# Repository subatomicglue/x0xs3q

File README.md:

# x0xs3q

We are creating a standalone [x0xb0x](https://www.ladyada.net/make/x0xb0x/) s3quencer.   **Please contribute!**

The idea is a single circuit board with power, USB, MIDI, track/pattern, and the sequencer section of the original x0xb0x.  Embeddable into many styles of case, but targeting a 303 style case to start.

## Features / Goals
- Control other synths via MIDI out:
  - Starting with the Behringer td-3, or midi enabled TB303
  - Also support other mono synths (SH-101, etc)
- Select button mapping with a switch:
  - x0xb0x: the more intuitive style of interface found on the stock x0xb0x (which promotes intentional composition)
  - 303: the more difficult tb303 / td3 style interface (which promotes "happy accidents")
- Slim 303 case
  - in the style of original Roland TB303
  - so that putting the x0xb0x sequencer in front of a TB303 or TD-3 looks like it belongs as a natural extension

## Concept

## Status

- Vaporware, you're looking at it, yes it's just a README so far... and ideas!
- Looking for contributors!

# copyright

this modification is built on the hard work of [Limor Freid](https://www.adafruit.com/about) & [Adafruit](https://www.adafruit.com/), and the [x0xb0x](https://www.ladyada.net/make/x0xb0x/) community

These files are all released under the [MIT Open Source license](http://en.wikipedia.org/wiki/MIT_License):

```
Copyright (c) Limor Fried & Adafruit industries

Permission is hereby granted, free of charge, to any person obtaining a copy of this software, firmware, layout and associated documentation files (the "Design files"), to deal in the Design files without restriction, including without limitation the rights to use, copy, modify, merge, publish, distribute, sublicense, and/or sell copies of the Design, and to permit persons to whom the Design is furnished to do so, subject to the following conditions: The above copyright notice and this permission notice shall be included in all copies or substantial portions of the Design.

THE DESIGN FILES ARE PROVIDED "AS IS", WITHOUT WARRANTY OF ANY KIND, EXPRESS OR IMPLIED, INCLUDING BUT NOT LIMITED TO THE WARRANTIES OF MERCHANTABILITY, FITNESS FOR A PARTICULAR PURPOSE AND NONINFRINGEMENT. IN NO EVENT SHALL THE AUTHORS OR COPYRIGHT HOLDERS BE LIABLE FOR ANY CLAIM, DAMAGES OR OTHER LIABILITY, WHETHER IN AN ACTION OF CONTRACT, TORT OR OTHERWISE, ARISING FROM, OUT OF OR IN CONNECTION WITH THE SOFTWARE OR THE USE OR OTHER DEALINGS IN THE SOFTWARE.
```

Notably:
```
If you plan to make, sell or manufacture x0xb0xes please contact us - we request that you credit Adafruit Industries on the documentation, supporting pages and circuit boards "Copyright (c) Limor Fried & Adafruit industries". x0xb0x (TM) is a trademarked name of Adafruit Industries. Please contact support@adafruit.com if you wish to seek permission to use the name for your products or projects, otherwise you cannot call your product "x0xb0x".
```

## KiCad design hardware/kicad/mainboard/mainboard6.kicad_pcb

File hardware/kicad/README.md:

# what's this

ladyada's original [x0xb0x](https://www.ladyada.net/make/x0xb0x/) mainboard and ioboard files were created with a version of EAGLE older than ver6.

EAGLE is now owned by autodesk, and is only available with FUSION 360 which costs money...

Let's use the excellent free/opensource KiCAD tool instead!

How we converted to KiCAD:
 - we loaded the original LadyAda mainboard and ioboard files into EAGLE 6 freeware, and saved.
 - we then imported the EAGLE6 files into KiCAD 5.1.2

enjoy

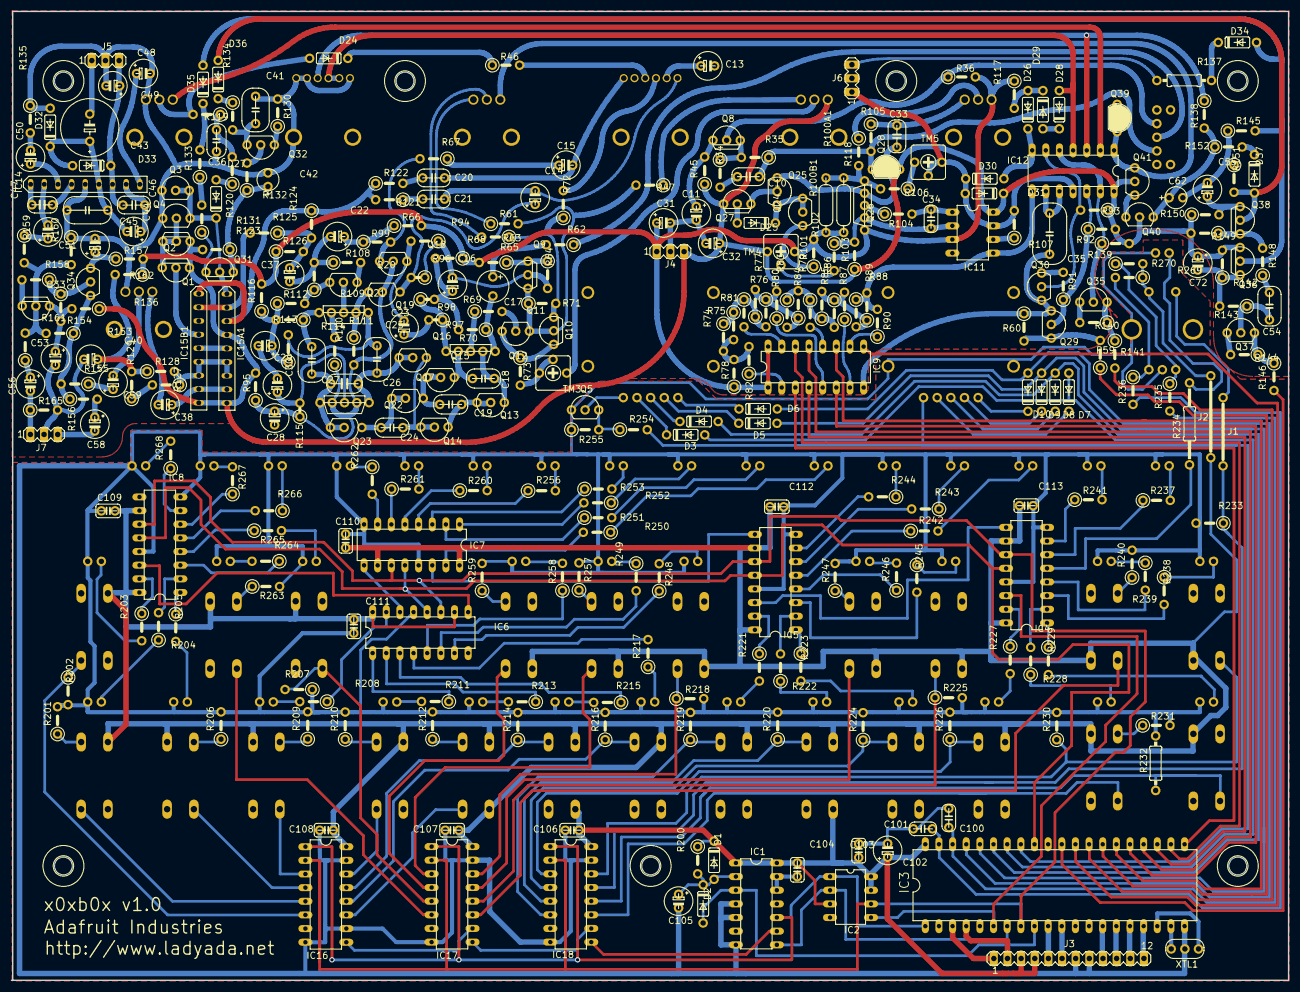
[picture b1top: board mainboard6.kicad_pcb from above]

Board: 16 copper layers, 237.5 x 180.3 mm, 417 parts (0 on the bottom side), 324 nets.

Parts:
C10, C20, C21, C33, C46: .01; C050-024X044
C11, C13, C14, C15, C22, C23, C29, C38, C56, C58, C59, C105: 1/50; E5-6
C16, C30, C31, C32, C37, C40, C50, C52, C72: 10/16; E5-6
C17: 1/50; E3,5-8
C18: .018; C050-025X075
C19, C24, C36: .033; C050-025X075
C25, C27, C41: .1; C050-030X075
C26: .033; C075-032X103
C28, C44, C53, C55: 47/16; E5-6
C34, C100, C101: .001; C050-035X075
C35: .22; C050-045X075
C42, C62: 1/35; E2,5-7
C43: 1000/6.3; E5-5
C45: .068; C050-050X075
C47: .0068; C050-075X075
C48, C49: 100/6.3; E5-6
C51: 2.2/50; E5-6
C54: .047; C050-055X075
C102: 100/10; E5-6
C103, C104, C106, C107, C108, C109, C110, C111, C112, C113: .1; C050H075X075
D1, D2, D3, D4, D5, D6, D7, D8, D9, D10, D24, D25, D26, D27, D28, D29, D30, D31, D32, D33, D34, D35, D36, D37: 1N4148; DO35-10
IC1: 74126N; DIL14
IC2: AT25P; DIL08
IC3: MEGA162P; DIL40
IC4, IC5, IC6, IC7, IC8: 74595N; DIL16
IC9: 4174P; DIL16
IC11: AN6562N; DIL08
IC12: 4066N; DIL14
IC14: LA44140; SIP9
IC15A1: BA662; SIP9
IC15B1: BA6110; SIP9
IC16, IC17, IC18: 74165N; DIL16
J1: J12MM; 12
J2: J15MM; 15
J3: MA12-1
J4, J5, J6, J7: MA03-1
LED1, LED2, LED3, LED4, LED5, LED6, LED7, LED8, LED9, LED10, LED11, LED12, LED13, LED14, LED15, LED16, LED17, LED18, LED19, LED20, LED21, LED22, LED23, LED24, LED25, LED26, LED27, LED28, LED29, LED30, LED31, LED32, LED33, LED34, LED35, LED36, LED37, LED38, LED39, LED40: LED5MM
Q1, Q2, Q8, Q9, Q10, Q27, Q31, Q33, Q36, Q38: 2SA733P; TO92
Q3, Q4, Q5, Q11, Q13, Q14, Q15, Q16, Q18, Q20, Q24, Q25, Q29, Q30, Q32, Q34, Q35, Q37, Q40, Q41: 2SC536F
Q12, Q21, Q26: 2SC1583; SSIP5
Q17, Q23: 2SC536F; 2SC536_UNEVEN
Q19: 2SC536FUNEVEN; 2SC536_UNEVEN
Q22: 2SC2291; SSIP5
Q28, Q39: 2SK30
R34, R36, R47, R61, R64, R65, R94, R101, R105, R109, R112, R116, R142, R143, R144, R145, R148, R149, R201, R202, R203, R204, R205, R206, R207, R208, R209, R210, R211, R212, R213, R214, R215, R216, R217, R218, R219, R220, R221, R222, R223, R224, R225, R226, R227, R228, R229, R230, R231, R233, R237, R238, R239, R240, R241, R242, R243, R244, R245, R246, R247, R248, R249, R250, R251, R252, R253, R254, R255, R256, R257, R258, R259, R260, R261, R262, R263, R264, R265, R266, R267, R268, R269, R270: 10K; 0207_5V
R35, R59, R66, R72, R73, R92, R93, R99, R102, R113, R114, R118, R122, R139, R140, R141, R154, R156, R165: 100K; 0207_5V
R45, R60, R110, R111, R117, R129, R134, R146, R151: 22K; 0207_5V
R46, R119, R127, R155: 47K; 0207_5V
R62, R63, R121, R128, R131: 220K; 0207_5V
R67, R68, R69, R70, R71, R104, R107, R108, R124, R125, R126, R133, R162: 2.2K; 0207_5V
R74, R75, R76, R77, R78, R79, R80, R81, R82, R83, R84, R85, R86, R87, R88, R89: 200K; 0207_5V
R90: 200k; 0207_5V
R91, R200: 1M; 0207_5V
R95, R130, R132, R136, R152: 100; 0207_5V
R96, R97, R115: 10K; 0207_2V
R98: 2.2K; 0207_2V
R100A1, R100B1: THERMISTOR-7,5; R-7,5
R103, R235, R236: 220k; 0207_5V
R106: 27K; 0207_5V
R120: 22k; 0207_5V
R123: 1.5M; 0207_5V
R135: 4.7k; 0207_5V
R137: 1K; 0207_10
R138: 68K; 0207_5V
R150: 22; 0207_5V
R153: 100k; 0207_5V
R157, R158, R160: 10k; 0207_5V
R159: 33K; 0207_5V
R161: 1K; 0207_5V
R232: 10K; 0207_10
R234: 10K; 0207_15
S1: SWITCH_GND; NKKTOGGLE
S2: PEC11-S
S3, S4: GH3074
S5, S6, S7, S8, S9, S10, S11, S12, S13, S14, S15, S16, S17, S18, S19, S20, S21, S22, S23, S24, S25, S26, S27: 40-XX; B3F-40XX
TM3: 500K(B); 306
TM4: 50K(B); 306
TM5: 5K(B); 306
U$2, U$23, U$24, U$25, U$27, U$28, U$29: 1,3
VR2, VR7: 50K(B); EVU
VR3, VR5, VR8: 50K(A); EVU
VR4: 50K(B); ALPHADUAL
VR6: 1M(A); ALPHADUAL
XTL1: 2SC2021R; 2SC2021

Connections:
+5.333V: C31.+, IC9.1, IC9.16, IC11.3, J4.1, Q26.1, R36.2, R65.2, R66.2, R68.1, R78.1, R100A1.2, R100B1.1, R101.2, R116.2, R117.1, R126.1, R157.2, R162.1, TM4.3, VR2.3
+5V: C102.+, C103.1, C104.2, C106.2, C107.2, C108.2, C109.2, C110.2, C111.2, C112.2, C113.2, D1.C, IC1.1, IC1.14, IC2.3, IC2.7, IC2.8, IC3.40, IC4.10, IC4.16, IC5.10, IC5.16, IC6.10, IC6.16, IC7.10, IC7.16, IC8.10, IC8.16, IC16.16, IC17.16, IC18.16, J2.2, J3.3, J3.4, R200.1, S5.2, S6.3, S7.1, S8.1, S9.1, S10.1, S11.1, S12.4, S13.4, S14.2, S15.4, S16.4, S17.2, S18.2, S19.1, S19.2, S20.2, S21.2, S22.1, S22.2, S23.1, S23.2, S24.2, S25.4, S26.4, S27.2
+6V: C46.1, C49.+, D33.C, IC14.7, J5.3
+12V: C32.+, C72.+, D31.C, IC11.8, IC12.14, IC15A1.4, IC15A1.9, IC15B1.9, J4.3, Q1.3, Q2.3, Q27.3, Q28.1, Q36.3, Q40.2, Q41.2, R45.1, R92.2, R93.1, R95.2, R103.1, R123.2, R136.1, R139.2, R142.2, R149.2, R150.1, TM4.1, VR3.3
/ACCENT: IC3.28, R141.2
/DINSYNC1: IC3.17, J3.12
/DINSYNC2: IC3.16, J3.11
/DINSYNC3: IC3.15, J3.10
/DINSYNC4: IC3.14, J3.9
/GATE: IC3.30, R146.2
/LED_LATCH: IC3.32, IC4.12, IC5.12, IC6.12, IC7.12, IC8.12
/MIDI_IN: IC3.10, J3.5
/MIDI_OUT: IC3.11, J3.6
/NOTE0: IC3.21, IC9.3
/NOTE1: IC3.22, IC9.14
/NOTE2: IC3.23, IC9.4
/NOTE3: IC3.24, IC9.13
/NOTE4: IC3.25, IC9.6
/NOTE5: IC3.26, IC9.11
/NOTE_LATCH: IC3.29, IC9.9
/ROTARY1: D3.A, D7.A, IC3.34
/ROTARY2: D4.A, D8.A, IC3.35
/ROTARY4: D5.A, D9.A, IC3.36
/ROTARY8: D6.A, D10.A, IC3.37
/ROTARYCOM3: IC3.33, R254.2, S3.C
/SLIDE: IC3.27, R59.1
/SPI_CLK: IC2.6, IC3.8, IC4.11, IC5.11, IC6.11, IC7.11, IC8.11, IC16.2, IC17.2, IC18.2
/SPI_IN: IC2.5, IC3.6, IC4.14
/SPI_OUT: IC1.8, IC2.2, IC3.7
/SWITCH_LATCH: IC1.10, IC2.1, IC3.1, IC16.1, IC17.1, IC18.1
/TEMPO_SW: IC18.13, J1.2, R233.1
/TEMPO_SW_A: C100.2, IC3.38, R235.2
/TEMPO_SW_B: C101.2, IC3.39, R236.2
/USBRX: IC3.3, J3.1
/USB_TX: IC3.4, J3.2
GND: C11.-, C13.-, C16.-, C22.-, C28.-, C29.-, C30.-, C31.-, C32.-, C33.2, C35.2, C36.2, C37.-, C40.-, C41.2, C42.-, C45.2, C48.-, C49.-, C52.-, C53.-, C55.-, C62.-, C100.1, C101.1, C102.-, C103.2, C104.1, C105.-, C106.1, C107.1, C108.1, C109.1, C110.1, C111.1, C112.1, C113.1, D26.C, D30.A, D32.A, IC1.4, IC1.5, IC1.7, IC1.12, IC1.13, IC2.4, IC3.20, IC4.8, IC4.13, IC5.8, IC5.13, IC6.8, IC6.13, IC7.8, IC7.13, IC8.8, IC8.13, IC9.8, IC11.4, IC12.7, IC14.5, IC15A1.5, IC15B1.3, IC15B1.5, IC16.8, IC16.10, IC16.15, IC17.8, IC17.15, IC18.8, IC18.15, J3.7, J3.8, J4.2, J5.2, J6.2, J7.2, LED1.K, LED2.K, LED3.K, LED4.K, LED5.K, LED6.K, LED7.K, LED8.K, LED9.K, LED10.K, LED11.K, LED12.K, LED13.K, LED14.K, LED15.K, LED16.K, LED17.K, LED18.K, LED19.K, LED20.K, LED21.K, LED22.K, LED23.K, LED24.K, LED25.K, LED26.K, LED27.K, LED28.K, LED29.K, LED30.K, LED31.K, LED32.K, LED33.K, LED34.K, LED35.K, LED36.K, LED37.K, LED38.K, LED39.K, LED40.K, Q3.3, Q4.3, Q5.3, Q9.2, Q29.3, Q30.3, Q35.3, Q37.3, Q39.2, Q39.3, R60.1, R64.2, R94.1, R96.1, R105.1, R108.1, R109.2, R130.2, R135.1, R140.2, R144.2, R145.1, R151.1, R160.1, R165.2, R201.2, R202.2, R206.2, R207.1, R209.2, R210.2, R212.2, R214.2, R216.2, R218.2, R219.2, R220.2, R224.2, R225.2, R226.2, R230.2, R231.2, R232.2, R233.2, R240.2, R247.2, R255.1, R257.2, R259.2, R263.2, S1.M1, S1.M2, S1.M3, S1.M4, S2.C, S2.P$1, S2.P$2, S3.MT1, S3.MT2, S3.MT3, S3.MT4, S4.MT1, S4.MT2, S4.MT3, S4.MT4, VR2.1, VR2.M1, VR2.M2, VR3.M1, VR3.M2, VR4.1A, VR4.M1, VR4.M2, VR5.M1, VR5.M2, VR6.1A, VR6.2A, VR6.3A, VR6.M1, VR6.M2, VR7.1, VR7.M1, VR7.M2, VR8.1, VR8.M1, VR8.M2, XTL1.2
unnamed: C10.1, Q28.3, R35.1, R105.2, S1.1
unnamed: C10.2, R34.2
unnamed: C11.+, Q8.3, R45.2
unnamed: C13.+, VR4.3B
unnamed: C14.+, Q19.3, R96.2
unnamed: C14.-, C21.2, VR4.3A
unnamed: C15.+, R67.1
unnamed: C15.-, C20.2, VR4.2A
unnamed: C16.+, R68.2, R70.2, R98.2
unnamed: C17.+, R62.2
unnamed: C17.-, Q12.1, R70.1
unnamed: C18.1, Q12.4, Q15.3
unnamed: C18.2, Q12.2, Q13.3
unnamed: C19.1, Q13.1, Q13.2, Q14.3
unnamed: C19.2, Q15.1, Q15.2, Q17.3
unnamed: C20.1, R122.2
unnamed: C21.1, R121.1
unnamed: C22.+, R66.1, R99.1
unnamed: C23.+, R97.2
unnamed: C23.-, R94.2
unnamed: C24.1, Q14.1, Q14.2, Q16.3
unnamed: C24.2, Q17.1, Q17.2, Q23.3
unnamed: C25.1, C26.1, Q16.1, Q16.2, Q22.1
unnamed: C25.2, Q21.1, R114.2
unnamed: C26.2, C27.1, Q22.5, Q23.1, Q23.2
unnamed: C27.2, Q21.5, R113.1
unnamed: C28.+, Q18.2, Q19.2, Q22.2, Q22.4, R95.1, R110.2, R111.1, R115.1
unnamed: C29.+, R112.1, R113.2, R114.1, R116.1
unnamed: C30.+, Q22.3, R115.2
unnamed: C33.1, Q25.3, Q26.4, Q28.2
unnamed: C34.1, IC11.1, R104.2
unnamed: C34.2, IC11.2, Q26.2, R102.1, R103.2
unnamed: C35.1, IC12.9, IC12.10
unnamed: C36.1, R119.1, R120.2
unnamed: C37.+, R124.2, R125.1, R126.2
unnamed: C38.+, IC15A1.8, IC15B1.8
unnamed: C38.-, VR8.3
unnamed: C40.+, R128.1, R162.2
unnamed: C41.1, Q32.1, R134.2
unnamed: C42.+, Q31.1, R123.1, R132.1
unnamed: C43.+, C44.-, C45.1, D32.C, D33.A, IC14.6
unnamed: C43.-, J5.1
unnamed: C44.+, C46.2, IC14.8
unnamed: C47.1, IC14.4
unnamed: C47.2, IC14.1
unnamed: C48.+, IC14.9
unnamed: C50.+, IC14.3
unnamed: C50.-, R135.2
unnamed: C51.+, R159.1
unnamed: C51.-, IC14.2
unnamed: C52.+, Q34.1, R157.1
unnamed: C53.+, Q33.3, R136.2, R154.2
unnamed: C54.1, R148.1
unnamed: C54.2, Q37.2, R143.1
unnamed: C55.+, Q38.3, R150.2
unnamed: C56.+, R161.1
unnamed: C58.+, R156.2
unnamed: C58.-, J7.3
unnamed: C59.+, R155.1
unnamed: C59.-, VR8.2
unnamed: C62.+, Q40.1, R138.2, R152.1
unnamed: C105.+, D1.A, D2.C, IC1.2, R200.2
unnamed: D2.A, IC1.3, IC3.9
unnamed: D3.C, S4.P$1
unnamed: D4.C, S4.P$2
unnamed: D5.C, S4.P$4
unnamed: D6.C, S4.P$8
unnamed: D7.C, S3.P$1
unnamed: D8.C, S3.P$2
unnamed: D9.C, S3.P$4
unnamed: D10.C, S3.P$8
unnamed: D24.A, R119.2, VR7.2
unnamed: D24.C, R46.1
unnamed: D25.A, Q27.2
unnamed: D25.C, Q24.1, Q24.2, Q25.1
unnamed: D26.A, D29.C, R117.2
unnamed: D27.A, R120.1
unnamed: D27.C, IC15A1.1, Q3.1, Q3.2, Q4.1, Q31.2
unnamed: D28.A, IC12.4, VR6.2B, VR6.3B
unnamed: D28.C, D29.A
unnamed: D30.C, D31.A, IC11.7, IC12.11, J6.1, R107.2, TM5.2, TM5.3
unnamed: D34.A, D35.A, Q36.2, R145.2
unnamed: D34.C, R137.1
unnamed: D35.C, R133.2
unnamed: D36.A, D37.A, Q38.2, R151.2
unnamed: D36.C, R134.1
unnamed: D37.C, R152.2
unnamed: IC1.9, IC18.9
unnamed: IC3.18, XTL1.3
unnamed: IC3.19, XTL1.1
unnamed: IC4.1, R229.1
unnamed: IC4.2, R228.2
unnamed: IC4.3, R238.2
unnamed: IC4.4, R239.2
unnamed: IC4.5, R234.1
unnamed: IC4.6, R237.1
unnamed: IC4.7, R241.1
unnamed: IC4.9, IC5.14
unnamed: IC4.15, R227.1
unnamed: IC5.1, R223.1
unnamed: IC5.2, R222.2
unnamed: IC5.3, R245.2
unnamed: IC5.4, R246.1
unnamed: IC5.5, R242.1
unnamed: IC5.6, R243.2
unnamed: IC5.7, R244.2
unnamed: IC5.9, IC7.14
unnamed: IC5.15, R221.1
unnamed: IC6.1, R211.1
unnamed: IC6.2, R213.1
unnamed: IC6.3, R215.1
unnamed: IC6.4, R217.2
unnamed: IC6.5, R258.1
unnamed: IC6.6, R249.2
unnamed: IC6.7, R248.1
unnamed: IC6.9, IC8.14
unnamed: IC6.14, IC7.9
unnamed: IC6.15, R208.1
unnamed: IC7.1, R252.2
unnamed: IC7.2, R251.1
unnamed: IC7.3, R253.1
unnamed: IC7.4, R256.1
unnamed: IC7.5, R260.1
unnamed: IC7.6, R261.1
unnamed: IC7.7, R262.2
unnamed: IC7.15, R250.2
unnamed: IC8.1, R205.1
unnamed: IC8.2, R204.2
unnamed: IC8.3, R264.1
unnamed: IC8.4, R265.1
unnamed: IC8.5, R266.2
unnamed: IC8.6, R267.1
unnamed: IC8.7, R268.1
unnamed: IC8.15, R203.1
unnamed: IC9.2, R82.1
unnamed: IC9.5, R80.1
unnamed: IC9.7, R87.1
unnamed: IC9.10, R90.1
unnamed: IC9.12, R79.2
unnamed: IC9.15, R81.2
unnamed: IC11.5, IC12.8, R88.1, R89.2, R90.2
unnamed: IC11.6, R107.1
unnamed: IC12.1, Q39.1, Q41.3, VR5.3
unnamed: IC12.2, VR7.3
unnamed: IC12.3, R138.1, VR6.1B
unnamed: IC12.6, Q30.2, R93.2
unnamed: IC12.12, Q29.2, R91.1, R92.1
unnamed: IC12.5, IC12.13, Q35.2, R139.1
unnamed: IC15A1.2, IC15B1.2, R125.2
unnamed: IC15A1.3, IC15B1.1, R121.2, R122.1, R124.1
unnamed: IC15A1.6, IC15A1.7, IC15B1.6, IC15B1.7, R127.1, R128.2
unnamed: IC15B1.4, Q1.2
unnamed: IC16.3, S25.1
unnamed: IC16.4, S26.1
unnamed: IC16.5, S27.3
unnamed: IC16.6, R202.1, S14.3
unnamed: IC16.9, IC17.10
unnamed: IC16.11, S23.3
unnamed: IC16.12, R216.1, S21.4
unnamed: IC16.13, R214.1, S22.4
unnamed: IC16.14, S24.3
unnamed: IC17.3, S10.3
unnamed: IC17.4, S11.3
unnamed: IC17.5, R207.2, S12.1
unnamed: IC17.6, S13.1
unnamed: IC17.9, IC18.10
unnamed: IC17.11, S6.1
unnamed: IC17.12, R225.1, S7.3
unnamed: IC17.13, S8.3
unnamed: IC17.14, R218.1, S9.3
unnamed: IC18.3, R226.1, S17.4
unnamed: IC18.4, R224.1, S18.4
unnamed: IC18.5, R220.1, S19.4
unnamed: IC18.6, R219.1, S20.4
unnamed: IC18.11, S16.1
unnamed: IC18.12, R232.1, S15.1
unnamed: IC18.14, R230.1, S5.4
unnamed: J1.1, S2.SW1
unnamed: J2.1, R269.1, R270.2, S2.SW2
unnamed: J6.3, R137.2
unnamed: J7.1, R165.1
unnamed: LED1.A, R234.2
unnamed: LED2.A, R237.2
unnamed: LED3.A, R241.2
unnamed: LED4.A, R242.2
unnamed: LED5.A, R243.1
unnamed: LED6.A, R244.1
unnamed: LED7.A, R250.1
unnamed: LED8.A, R251.2
unnamed: LED9.A, R252.1
unnamed: LED10.A, R253.2
unnamed: LED11.A, R256.2
unnamed: LED12.A, R260.2
unnamed: LED13.A, R261.2
unnamed: LED14.A, R262.1
unnamed: LED15.A, R266.1
unnamed: LED16.A, R267.2
unnamed: LED17.A, R268.2
unnamed: LED18.A, R238.1
unnamed: LED19.A, R239.1
unnamed: LED20.A, R245.1
unnamed: LED21.A, R246.2
unnamed: LED22.A, R248.2
unnamed: LED23.A, R249.1
unnamed: LED24.A, R258.2
unnamed: LED25.A, R265.2
unnamed: LED26.A, R264.2
unnamed: LED27.A, R203.2
unnamed: LED28.A, R229.2
unnamed: LED29.A, R228.1
unnamed: LED30.A, R227.2
unnamed: LED31.A, R223.2
unnamed: LED32.A, R222.1
unnamed: LED33.A, R221.2
unnamed: LED34.A, R217.1
unnamed: LED35.A, R215.2
unnamed: LED36.A, R213.2
unnamed: LED37.A, R211.2
unnamed: LED38.A, R208.2
unnamed: LED39.A, R205.2
unnamed: LED40.A, R204.1
unnamed: Q1.1, Q2.1, Q2.2, Q4.2
unnamed: Q5.1, R254.1, R255.2
unnamed: Q5.2, S4.C
unnamed: Q8.1, R34.1, R35.2
unnamed: Q8.2, R36.1, S1.3
unnamed: Q9.1, R64.1, R65.1
unnamed: Q10.1, R63.1, R71.2, R72.1
unnamed: Q9.3, Q10.2, Q11.3, R47.2, R61.2, R71.1
unnamed: Q10.3, R73.1
unnamed: Q11.2, R69.2
unnamed: Q12.3, R69.1
unnamed: Q12.5, R97.1, R98.1
unnamed: Q18.1, R67.2, R99.2
unnamed: Q19.1, Q21.2, R110.1
unnamed: Q20.1, R109.1, R112.2
unnamed: Q20.2, Q21.3
unnamed: Q20.3, R108.2
unnamed: Q21.4, R111.2
unnamed: Q24.3, R101.1
unnamed: Q25.2, Q27.1
unnamed: Q26.3, R104.1
unnamed: Q26.5, R100A1.1, R100B1.2, R106.2, R118.2
unnamed: Q29.1, R59.2, R60.2
unnamed: Q30.1, R91.2
unnamed: Q31.3, R131.1
unnamed: Q32.2, R132.2
unnamed: Q32.3, R130.1
unnamed: Q33.1, R158.2
unnamed: Q33.2, R153.2, R159.2, R160.2, R161.2
unnamed: Q34.2, R154.1, R158.1
unnamed: Q34.3, R153.1, R155.2, R156.1
unnamed: Q35.1, R140.1, R141.1
unnamed: Q36.1, R142.1, R143.2
unnamed: Q37.1, R144.1, R146.1
unnamed: Q38.1, R148.2, R149.1
unnamed: Q40.3, Q41.1
unnamed: R46.2, VR4.1B
unnamed: R47.1, VR3.1
unnamed: R61.1, VR5.1
unnamed: R62.1, S1.2
unnamed: R63.2, VR5.2
unnamed: R72.2, VR4.2B
unnamed: R73.2, TM3.2, TM3.3
unnamed: R74.1, R75.1, R76.1, R77.2, R81.1
unnamed: R74.2, R75.2, R78.2, R82.2
unnamed: R76.2, R77.1, R80.2, R83.2, R84.1
unnamed: R79.1, R83.1, R84.2, R85.1, R86.2
unnamed: R85.2, R86.1, R87.2, R88.2, R89.1
unnamed: R102.2, TM4.2
unnamed: R106.1, TM5.1
unnamed: R118.1, VR2.2
unnamed: R127.2, R129.1
unnamed: R131.2, R133.1
unnamed: R201.1, S27.4
unnamed: R206.1, S26.2
unnamed: R209.1, S25.2
unnamed: R210.1, S24.4
unnamed: R212.1, S23.4
unnamed: R231.1, S16.2
unnamed: R235.1, R270.1, S2.A
unnamed: R236.1, R269.2, S2.B
unnamed: R240.1, S6.2
unnamed: R247.1, S8.4
unnamed: R257.1, S10.4
unnamed: R259.1, S11.4
unnamed: R263.1, S13.2
unnamed: TM3.1, VR3.2

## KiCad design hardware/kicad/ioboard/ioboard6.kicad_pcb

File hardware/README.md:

# hardware

the hardware for the x0xb0x

# copyright

this modification is built on the hard work of Limor Freid & Adafruit, and the x0xb0x community

These files are all released under the [MIT Open Source license](http://en.wikipedia.org/wiki/MIT_License):

```
Copyright (c) Limor Fried & Adafruit industries

Permission is hereby granted, free of charge, to any person obtaining a copy of this software, firmware, layout and associated documentation files (the "Design files"), to deal in the Design files without restriction, including without limitation the rights to use, copy, modify, merge, publish, distribute, sublicense, and/or sell copies of the Design, and to permit persons to whom the Design is furnished to do so, subject to the following conditions: The above copyright notice and this permission notice shall be included in all copies or substantial portions of the Design.

THE DESIGN FILES ARE PROVIDED "AS IS", WITHOUT WARRANTY OF ANY KIND, EXPRESS OR IMPLIED, INCLUDING BUT NOT LIMITED TO THE WARRANTIES OF MERCHANTABILITY, FITNESS FOR A PARTICULAR PURPOSE AND NONINFRINGEMENT. IN NO EVENT SHALL THE AUTHORS OR COPYRIGHT HOLDERS BE LIABLE FOR ANY CLAIM, DAMAGES OR OTHER LIABILITY, WHETHER IN AN ACTION OF CONTRACT, TORT OR OTHERWISE, ARISING FROM, OUT OF OR IN CONNECTION WITH THE SOFTWARE OR THE USE OR OTHER DEALINGS IN THE SOFTWARE.
```

Notably:
```
If you plan to make, sell or manufacture x0xb0xes please contact us - we request that you credit Adafruit Industries on the documentation, supporting pages and circuit boards "Copyright (c) Limor Fried & Adafruit industries". x0xb0x (TM) is a trademarked name of Adafruit Industries. Please contact support@adafruit.com if you wish to seek permission to use the name for your products or projects, otherwise you cannot call your product "x0xb0x".
```

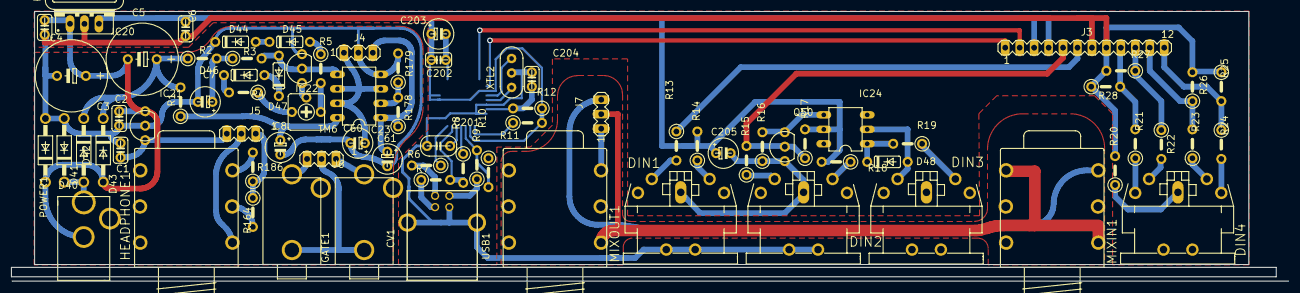
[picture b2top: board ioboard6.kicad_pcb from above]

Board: 16 copper layers, 224.4 x 47.4 mm, 82 parts (0 on the bottom side), 57 nets.

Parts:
C1, C2, C4, C6: .1; C050H075X075
C3, C5: 2200/16; E5-13
C7, C8: 100/25; E5-6
C60, C61: 10/16; E5-6
C201: 33nF; C050-025X075
C202, C204: .1uF; C050H075X075
C203, C205: 10uF; E5-6
CV1: MONO_CC; CP-3502
D40, D41, D42, D43: 1N4001; DO41-10
D44, D45, D46, D47, D48: 1N4148; DO35-10
DIN1, DIN2, DIN3, DIN4: CP2350; CP-2350
GATE1: MONO_CC; CP-3502
HEADPHONE1: NEUTRIX_STEREO; REAN_1_4STERO
IC20: 7805; 78XXS
IC21: 78L06Z; 2SC536F
IC22: LM336Z-5.0; 2SC536F
IC23: AN6562N; DIL08
IC24: 4N37; DIL06
IC25: FT232; SQFP-S-7X7-32
J3: MA12-1
J4, J5, J6, J7: MA03-1
KK1: D03S
MIXIN1: NEUTRIX_STEREO; REAN_1_4STERO
MIXOUT1: NEUTRIX_STEREO; REAN_1_4STERO
POWER1: 2.1MMJACK; PJ-102A
Q50: 2SC536F
R1, R16: 100; 0207_5V
R2, R17: 1k; 0207_5V
R3: 6.8k; 0207_5V
R4: 5.6k; 0207_5V
R5: 2.4k; 0207_5V
R6, R7: 27; 0207_5V
R8: 1.5k; 0207_5V
R9: 4.7k; 0207_5V
R10: 10k; 0207_5V
R11: 10K; 0207_5V
R12: 470; 0207_5V
R13, R14, R15, R18, R19: 220; 0207_5V
R20: 22; 0207_5V
R21, R22, R23, R24: 2.2K; 0207_5V
R25, R26, R27, R28: 100K; 0207_5V
R164, R186: 10; 0207_5V
R178: 2.2k; 0207_5V
R179: 1.8k; 0207_5V
TM6: 2k; 306
USB1: ACON_TYPEB; PN61729
XTL2: 6.00MHz; CERM_OSC

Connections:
+5.333V: C60.+, IC23.3, IC23.6, IC23.7, J4.1
+5V: C6.1, C202.1, C203.+, C205.+, IC20.OUT, IC24.5, IC25.3, IC25.13, IC25.14, IC25.26, J3.3, J3.4, R11.2, R12.1, R14.2, R17.2, R18.2
+6V: C1.1, IC21.3, J5.3
+12V: C61.+, IC23.1, J4.3, R178.1
/DINSYNC1: J3.12, R24.1, R25.2
/DINSYNC2: J3.11, R23.2, R26.1
/DINSYNC3: J3.10, R22.1, R27.1
/DINSYNC4: J3.9, R21.2, R28.2
/MIDI_IN: J3.5, Q50.2, R15.2, R17.1
/MIDI_OUT: J3.6, R13.1
/USB_RX: IC25.24, J3.2
/USB_TX: IC25.25, J3.1
GND: C1.2, C2.2, C3.-, C4.2, C6.2, C7.-, C8.-, C60.-, C61.-, C201.2, C202.2, C203.-, C204.2, C205.-, CV1.SLEEVE, D40.A, D41.A, D44.C, DIN1.2, DIN1.PE, DIN1.PE@, DIN2.2, DIN2.PE, DIN2.PE@, GATE1.SLEEVE, HEADPHONE1.S, IC20.GND, IC21.2, IC22.3, IC23.4, IC25.9, IC25.17, IC25.29, IC25.31, J3.7, J3.8, J4.2, J5.2, J6.2, J7.2, MIXIN1.S, MIXIN1.TN, MIXOUT1.S, Q50.3, R10.1, R16.1, R20.2, R25.1, R26.2, R27.2, R28.1, R179.2, USB1.4, USB1.M2, USB1.P$2
unnamed: C2.1, C3.+, C4.1, C5.-, D40.C, D43.A, IC20.IN, POWER1.P$2
unnamed: C5.+, D42.C, D43.C, R1.2, R2.1
unnamed: C7.+, R2.2, R3.1
unnamed: C8.+, IC23.8, R1.1
unnamed: C201.1, IC25.6
unnamed: C204.1, IC25.30, R12.2
unnamed: CV1.TIP, J6.1
unnamed: D41.C, D42.A, POWER1.P$1
unnamed: D44.A, D45.C
unnamed: D45.A, R5.1
unnamed: D46.A, D47.C
unnamed: D46.C, R4.2
unnamed: D47.A, IC22.2, IC23.5, R3.2
unnamed: D48.A, DIN3.5, IC24.2
unnamed: D48.C, IC24.1, R19.2
unnamed: DIN1.4, R14.1
unnamed: DIN1.5, R13.2
unnamed: DIN2.4, R18.1
unnamed: DIN2.5, R15.1
unnamed: DIN3.4, R19.1
unnamed: DIN4.1, R24.2
unnamed: DIN4.2, R20.1
unnamed: DIN4.3, R21.1
unnamed: DIN4.4, R23.1
unnamed: DIN4.5, R22.2
unnamed: GATE1.TIP, J6.3
unnamed: HEADPHONE1.R, R164.2
unnamed: HEADPHONE1.T, R186.2
unnamed: IC22.1, TM6.2
unnamed: IC23.2, R178.2, R179.1
unnamed: IC24.4, Q50.1, R16.2
unnamed: IC25.2, R11.1
unnamed: IC25.4, R9.2, R10.2
unnamed: IC25.5, R8.1
unnamed: IC25.7, R7.2, R8.2
unnamed: IC25.8, R6.1
unnamed: J5.1, R164.1, R186.1
unnamed: J7.1, MIXOUT1.T
unnamed: J7.3, MIXIN1.T
unnamed: R4.1, TM6.3
unnamed: R5.2, TM6.1
unnamed: R6.2, USB1.2
unnamed: R7.1, USB1.3
unnamed: R9.1, USB1.1

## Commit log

2020-07-24 first import
2020-07-24 added title and windows section
2020-07-24 remove volume knob
2020-07-24 get this compiling with latest avr-gcc from macos homebrew package manager
2020-07-24 added copyright
2020-07-24 added link
2020-07-24 added links
2020-07-24 better concept
2020-07-24 convert boards to kicad
2020-07-24 added readme
2020-07-24 organize
